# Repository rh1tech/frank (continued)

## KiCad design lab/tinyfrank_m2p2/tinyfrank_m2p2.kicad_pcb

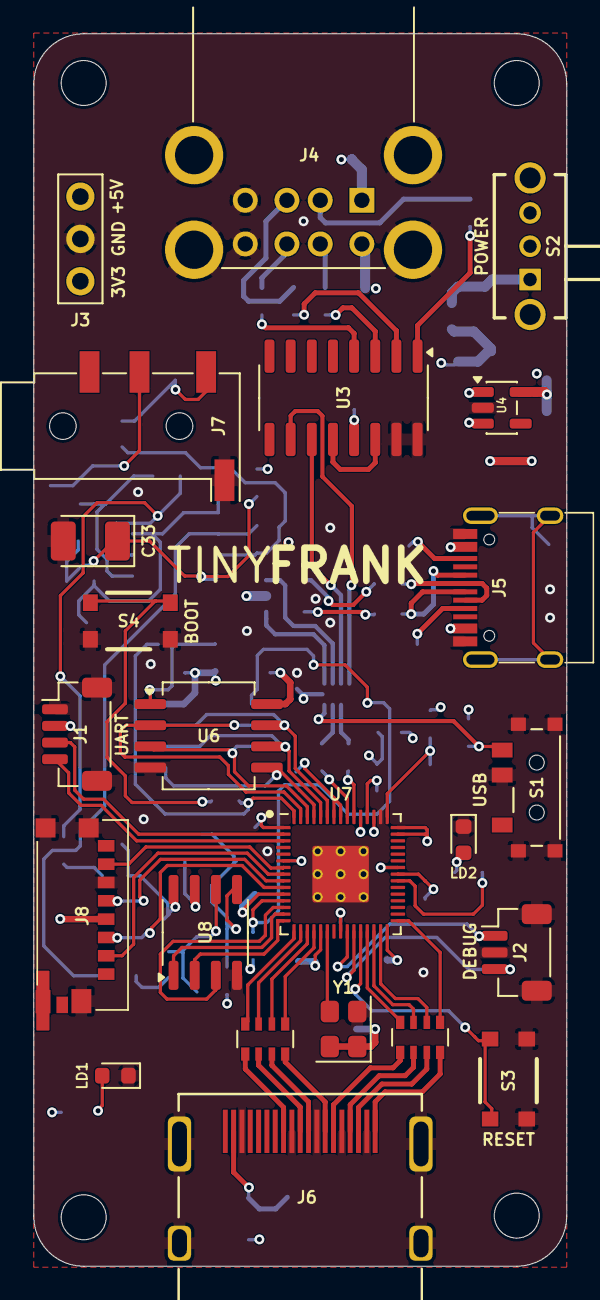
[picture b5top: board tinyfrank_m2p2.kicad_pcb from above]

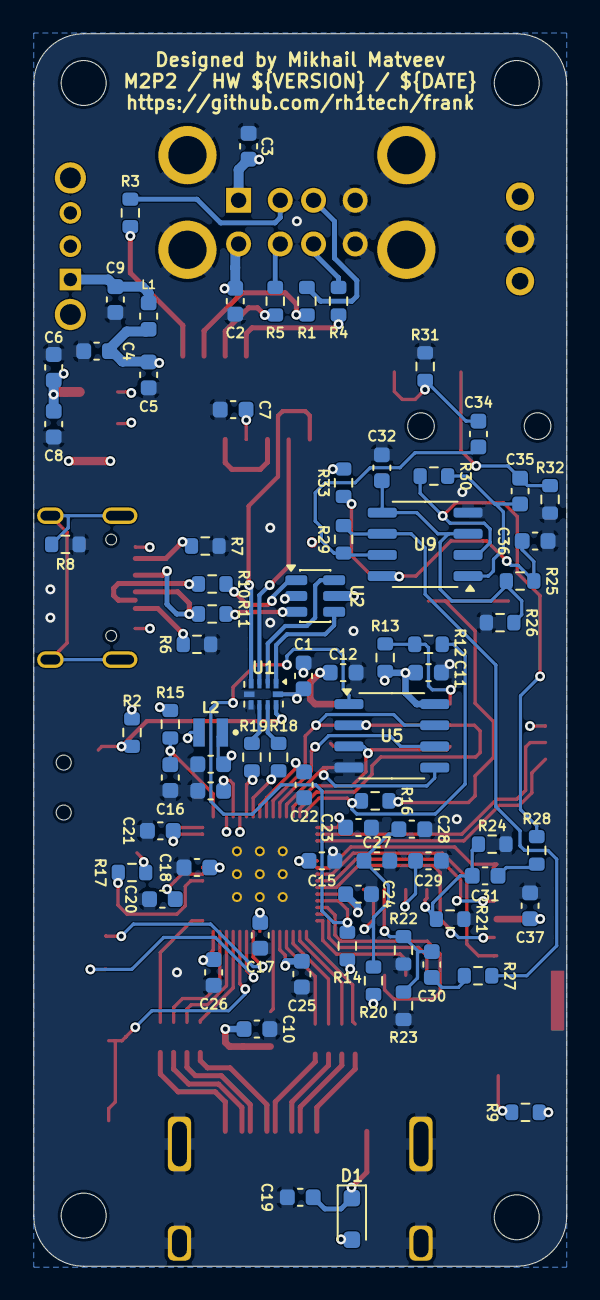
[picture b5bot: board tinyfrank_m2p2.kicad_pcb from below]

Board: 4 copper layers, 32.0 x 74.0 mm, 103 parts (76 on the bottom side), 89 nets.

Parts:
C1, C5, C6, C9, C10, C11, C12, C15, C18, C19, C20, C21, C22, C23, C24, C25, C26, C28, C36, C37: 100n; C_0603_1608Metric
C2, C3, C4, C8, C27, C29, C30, C31, C32, C34, C35: 10u; C_0603_1608Metric
C7, C13, C14, C16, C17: 4.7u; C_0603_1608Metric
C33: 10u; C_3528_Tantalum
D1: 1N5819WS; D_SOD-323
H1, H2, H3, H4: Hole 2.7mm; MountingHole_2.7mm
J1: UART; JST_SH_1x04_P1.00mm_Vertical
J2: DEBUG; JST_SH_1x03_P1.00mm_Vertical
J3: PWR; PinHeader_1x03_P2.54mm
J4: SS-52100-004; USB_A_Stacked
J5: USB4215-03-A; USB_C_Receptacle
J6: DC3RX19JA2; HDMI_Female
J7: PJ-320D; AudioJack_3.5mm_PJ320D
J8: 0475710001; MicroSD_SMD_Short
L1: 330R; L_0603_1608Metric
L2: 3.3u; L_2016_Polarized
LD1: Green; LED_0603_1608Metric
LD2: Blue; LED_0603_1608Metric
R1, R3, R4, R5, R10, R11: 22R; R_0603_1608Metric
R2, R13, R14, R23, R24, R25, R26, R27, R28: 10K; R_0603_1608Metric
R6, R7: 5.1K; R_0603_1608Metric
R8: 1M; R_0603_1608Metric
R9, R16, R17: 1K; R_0603_1608Metric
R12: 0R; R_0603_1608Metric
R15: 33R; R_0603_1608Metric
R18, R19: 27R; R_0603_1608Metric
R20, R33: 100R; R_0603_1608Metric
R21, R22: 470R; R_0603_1608Metric
R29, R30: 47K; R_0603_1608Metric
R31, R32: 20K; R_0603_1608Metric
RN1, RN2: 270R; R_Array_4x0603
S1: MSK12C02; Switch_Slide_MSK12C02
S2: SK12D07VG3NS; Switch_Slide_SK12D07VG3NS
S3, S4: Button; Button_SMD_3x4x2mm
U1: TS3USB221RSER; UQFN-10
U2: USBLC6-2SC6; SOT-23-6
U3: MW7211A; SOP-16_P1.27mm
U4: ME6211C33M5; SOT-23-5
U5: ESP-PSRAM32; SO-8
U6: W25Q128JVS; SOIC-8
U7: RP2350; QFN-60_RP2350A
U8: TDA1387T; SO-8
U9: LM358; SO-8
Y1: ASE-12MHz; Oscillator_SMD_Abracon_ASE-4Pin_3.2x2.5mm

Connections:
+1V1: C14.1, C15.1, C17.1, C18.1, L2.1, U7.6 (DVDD), U7.23 (DVDD), U7.39 (DVDD), U7.50 (VREG_FB)
+3V3: C1.2, C6.1, C8.1, C10.1, C11.1, C12.1, C13.1, C20.1, C21.1, C22.1, C23.1, C24.1, C25.1, C26.1, C37.2, J1.2, J3.1, J8.P4 (VDD), R2.1, R9.2, R13.1, R14.2, R15.1, U1.10 (VCC), U4.5 (V_{OUT}), U5.8 (VCC), U6.8 (VCC), U7.1 (IOVDD), U7.11 (IOVDD), U7.20 (IOVDD), U7.30 (IOVDD), U7.38 (IOVDD), U7.44 (ADC_AVDD), U7.45 (IOVDD), U7.49 (VREG_VIN), U7.53 (USB_OTP_VDD), U7.54 (QSPI_IOVDD), Y1.1 (EN), Y1.4 (Vdd)
/Audio/AMP_OUTL: C34.2, J7.T, R31.2
/Audio/AMP_OUTR: C35.2, J7.R, R32.2
/Audio/TDA_DATA: U7.13 (GPIO9), U8.3 (DATA)
/Audio/TDA_L: C30.1, R22.2, R23.1, U8.6 (A_LEFT)
/Audio/TDA_LRCK: U7.15 (GPIO11), U8.2 (LRCK)
/Audio/TDA_R: C31.1, R21.1, R24.1, U8.8 (A_RIGHT)
/Audio/TDA_SCLK: U7.14 (GPIO10), U8.1 (SCLK)
/HDMI/CLKN: RN1.4 (R4.1), U7.16 (GPIO12)
/HDMI/CLKP: RN1.3 (R3.1), U7.17 (GPIO13)
/HDMI/D0N: RN1.2 (R2.1), U7.18 (GPIO14)
/HDMI/D0P: RN1.1 (R1.1), U7.19 (GPIO15)
/HDMI/D1N: RN2.4 (R4.1), U7.27 (GPIO16)
/HDMI/D1P: RN2.3 (R3.1), U7.28 (GPIO17)
/HDMI/D2N: RN2.2 (R2.1), U7.29 (GPIO18)
/HDMI/D2P: RN2.1 (R1.1), U7.31 (GPIO19)
/Micro SD/CDDAT3: J8.P2 (CD/DAT3), U7.8 (GPIO5)
/Micro SD/CLK: J8.P5 (CLK), U7.9 (GPIO6)
/Micro SD/CMD: J8.P3 (CMD), U7.10 (GPIO7)
/Micro SD/DAT0: J8.P7 (DAT0), U7.7 (GPIO4)
/Power/D1+: U1.1 (1D+), U2.4 (I/O2)
/Power/D1-: U1.2 (1D-), U2.6 (I/O1)
/Power/D2+: U1.3 (2D+), U3.11 (DPU)
/Power/D2-: U1.4 (2D-), U3.10 (DMU)
/Power/D+: R18.1, U1.8 (D+)
/Power/D-: R19.1, U1.7 (D-)
/Power/DS1+: R1.1, U3.2 (DP0)
/Power/DS1-: R3.1, U3.1 (DM0)
/Power/DS2+: R4.1, U3.4 (DP1)
/Power/DS2-: R5.1, U3.3 (DM1)
/Power/S: R2.2, S1.3, U1.9 (S)
/Power/VBUS_IN: J5.2 (VBUS), J5.11 (VBUS), S2.2
/RP2350A/FLASH_SS: R12.2, R13.2, U6.1 (~CS)
/RP2350A/GPIO0: J1.3, U7.2 (GPIO0)
/RP2350A/GPIO1: J1.4, U7.3 (GPIO1)
/RP2350A/GPIO8: R14.1, U5.1 (~CE), U7.12 (GPIO8)
/RP2350A/QSPI_SCLK: U5.6 (SCLK), U6.6 (CLK), U7.56 (QSPI_SCLK)
/RP2350A/QSPI_SD0: U5.5 (SI/SIO), U6.5 (DI(IO0)), U7.57 (QSPI_SD0)
/RP2350A/QSPI_SD1: U5.2 (SO/SIO), U6.2 (DO(IO1)), U7.59 (QSPI_SD1)
/RP2350A/QSPI_SD2: U5.3 (SIO2), U6.3 (IO2), U7.58 (QSPI_SD2)
/RP2350A/QSPI_SD3: U5.7 (SIO3), U6.7 (IO3), U7.55 (QSPI_SD3)
/RP2350A/QSPI_SS: R12.1, R16.1, U7.60 (QSPI_SS)
/RP2350A/SWCLK: J2.1, U7.24 (SWCLK)
/RP2350A/SWD: J2.3, U7.25 (SWD)
/RP2350A/VREG_AVDD: C16.1, R15.2, U7.46 (VREG_AVDD)
/RP2350A/VREG_LX: L2.2, U7.48 (VREG_LX)
/RP2350A/XIN: U7.21 (XIN), Y1.3 (OUT)
/RP2350A/~USB_BOOT: R16.2, S4.2, S4.4
/RP Reset/C1: S3.2, S3.4, U7.26 (RUN)
GND: C1.1, C2.2, C3.2, C4.1, C5.1, C6.2, C7.2, C8.2, C9.2, C10.2, C11.2, C12.2, C13.2, C14.2, C15.2, C16.2, C17.2, C18.2, C19.2, C20.2, C21.2, C22.2, C23.2, C24.2, C25.2, C26.2, C27.2, C28.2, C29.2, C32.1, C33.2, C36.1, C37.1, J1.1, J1.MP (Shield), J2.2, J2.MP (Shield), J3.2, J4.4 (GND1), J4.8 (GND2), J4.SH (Shield), J5.1 (GND), J5.12 (GND), J6.2 (G_D2), J6.5 (G_D1), J6.8 (G_D0), J6.11 (G_CLK), J6.17 (G_DDC/CEC), J6.20 (SHIELD1), J6.21 (SHIELD2), J6.22 (SHIELD3), J6.23 (SHIELD4), J7.S, J8.P6 (VSS), J8.SH (GND_3), LD1.1 (K), LD2.1 (K), R6.1, R7.1, R8.2, R21.2, R22.1, R23.2, R24.2, R26.1, R31.1, R32.1, S1.2, S1.4 (GND_4), S3.1, S3.3, S4.1, S4.3, U1.5 (GND), U1.6 (~OE), U2.2 (GND), U3.15 (GND), U3.16 (GND), U4.2 (V_{SS}), U5.4 (VSS), U6.4 (GND), U7.47 (VREG_PGND), U7.61 (GND), U8.4 (AGND), U9.4 (V-), Y1.2 (GND)
GPIO25: R17.2, U7.37 (GPIO25)
unnamed: C9.1, L1.2, S2.1
unnamed: C30.2, R27.2
unnamed: C31.2, R28.2
unnamed: C34.1, R29.1, U9.7
unnamed: C35.1, R30.1, U9.1
unnamed: C19.1, D1.1 (K), J6.18 (+5V)
unnamed: J4.3 (D1+), R1.2
unnamed: J4.2 (D1-), R3.2
unnamed: J4.7 (D2+), R4.2
unnamed: J4.6 (D2-), R5.2
unnamed: J5.4 (CC1), R6.2
unnamed: J5.10 (CC2), R7.2
unnamed: J5.5 (DN2), J5.7 (DN1), R10.2
unnamed: J5.6 (DP1), J5.8 (DP2), R11.2
unnamed: J5.13 (SHIELD), R8.1
unnamed: J6.12 (CLKN), RN1.5 (R4.2)
unnamed: J6.10 (CLKP), RN1.6 (R3.2)
unnamed: J6.9 (D0N), RN1.7 (R2.2)
unnamed: J6.7 (D0P), RN1.8 (R1.2)
unnamed: J6.6 (D1N), RN2.5 (R4.2)
unnamed: J6.4 (D1P), RN2.6 (R3.2)
unnamed: J6.3 (D2N), RN2.7 (R2.2)
unnamed: J6.1 (D2P), RN2.8 (R1.2)
unnamed: LD1.2 (A), R9.1
unnamed: LD2.2 (A), R17.1
unnamed: R10.1, U2.1 (I/O1)
unnamed: R11.1, U2.3 (I/O2)
unnamed: U3.12 (VD33), U3.14 (VD3)
unnamed: R19.2, U7.51 (USB_DM)
unnamed: R18.2, U7.52 (USB_DP)
unnamed: C29.1, U8.7 (FLT)
unnamed: C27.1, C28.1, R20.1, U8.5 (VA)
unnamed: C32.2, R25.1, R26.2, U9.3 (+), U9.5 (+)
unnamed: R28.1, R30.2, U9.2 (-)
unnamed: R27.1, R29.2, U9.6 (-)
unnamed: C33.1, C36.2, R25.2, R33.2, U9.8 (V+)
VBUS: C2.1, C3.1, C4.2, C5.2, C7.1, D1.2 (A), J3.3, J4.1 (VBUS1), J4.5 (VBUS2), L1.1, R20.2, R33.1, U2.5 (VBUS), U3.13 (VDD5), U4.1 (V_{IN}), U4.3 (CE)

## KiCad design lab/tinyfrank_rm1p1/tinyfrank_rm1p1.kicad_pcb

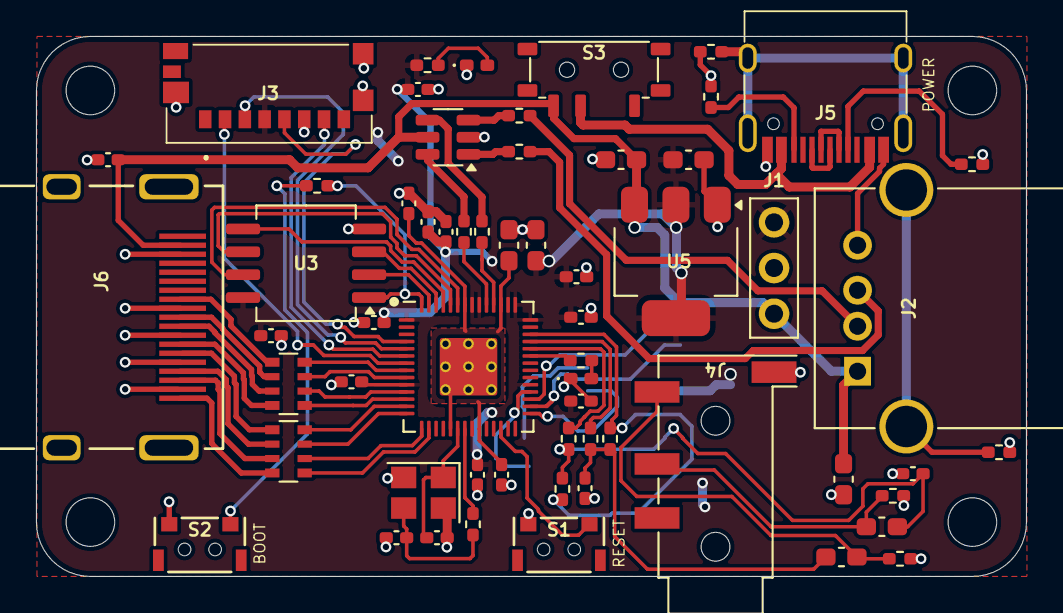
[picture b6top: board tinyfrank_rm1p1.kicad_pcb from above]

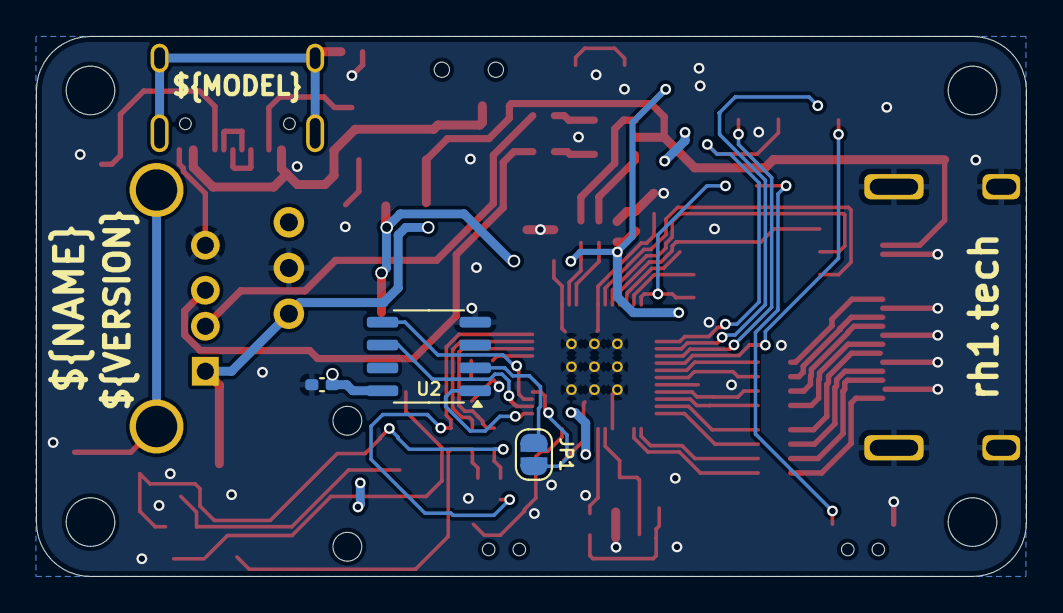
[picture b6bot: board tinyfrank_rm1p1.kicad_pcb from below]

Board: 2 copper layers, 55.0 x 30.0 mm, 67 parts (3 on the bottom side), 65 nets.

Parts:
C1, C3, C5, C23, C24: 10u; Capacitor (0603)
C2, C7, C8, C9, C10, C11, C12, C13, C14, C15, C16, C17, C20, C25: 100n; Capacitor (0402)
C4, C6: 10n; Capacitor (0402)
C18, C19: 1u; Capacitor (0603)
C21, C22: 15p; Capacitor (0402)
H1, H2, H3, H4: MountingHole; Mounting Hole (2.7mm)
J1: PWR; Pin Header (1x03)
J2: 676430910; USB Type A (single)
J3: 0475710001; MicroSD (SMD, short)
J4: PJ-320D; Jack (3.5mm, PJ-320D)
J5: USB4215-03-A; USB Type C
J6: DC3RX19JA2; HDMI (female)
JP1: Jumper (Solder); Jumper (solder)
LD1: Blue; LED (0402)
LD2: Power; LED (0402)
R1, R2: 22R; Resistor (0402)
R3, R17: 1M; Resistor (0402)
R4, R8, R11, R13, R14, R18: 1K; Resistor (0402)
R5, R9: 330R; Resistor (0402)
R6, R7: 2K; Resistor (0402)
R10, R12: 27R; Resistor (0402)
R15, R16: 5.1K; Resistor (0402)
RN1, RN2: 270R; Resistor Array (4x0603)
S1: Reset; TACT-SIDE-4623
S2: Boot; TACT-SIDE-4623
S3: MSK12C02; Switch (MSK12C02)
U1: USBLC6-2SC6; SOT-23-6
U2: ESP-PSRAM32; SO-8
U3: W25Q128JVSIQ; SOIC-8
U4: RP2040; QFN 56
U5: NCP1117 3.3; SOT-223
Y1: 12 MHz; Crystal (3225)

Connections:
+3V3: C2.2, C7.1, C10.1, C11.1, C12.1, C13.1, C14.1, C15.1, C16.1, C17.1, C19.1, C20.1, C23.1, J1.1, J3.P4 (VDD), R18.2, U2.8 (VCC), U3.8 (VCC), U4.1 (IOVDD), U4.10 (IOVDD), U4.22 (IOVDD), U4.33 (IOVDD), U4.42 (IOVDD), U4.43 (ADC_AVDD), U4.44 (VREG_IN), U4.48 (USB_VDD), U4.49 (IOVDD), U5.2 (VO)
/Audio Out/L: C3.1, J4.T, R5.1
/Audio Out/R: C5.1, J4.R, R9.1
/GPIO2: J3.P5 (CLK), U4.4 (GPIO2)
/GPIO3: J3.P3 (CMD), U4.5 (GPIO3)
/GPIO4: J3.P7 (DAT0), U4.6 (GPIO4)
/GPIO5: J3.P2 (CD/DAT3), U4.7 (GPIO5)
/GPIO6: RN1.4 (R4.1), U4.8 (GPIO6)
/GPIO7: RN1.3 (R3.1), U4.9 (GPIO7)
/GPIO8: RN1.2 (R2.1), U4.11 (GPIO8)
/GPIO9: RN1.1 (R1.1), U4.12 (GPIO9)
/GPIO10: RN2.4 (R4.1), U4.13 (GPIO10)
/GPIO11: RN2.3 (R3.1), U4.14 (GPIO11)
/GPIO12: RN2.2 (R2.1), U4.15 (GPIO12)
/GPIO13: RN2.1 (R1.1), U4.16 (GPIO13)
/GPIO18: U2.1 (~CE), U4.29 (GPIO18)
/GPIO19: U2.6 (SCLK), U4.30 (GPIO19)
/GPIO20: U2.5 (SI/SIO), U4.31 (GPIO20)
/GPIO21: JP1.2 (B), U4.32 (GPIO21)
/GPIO25: R14.2, U4.37 (GPIO25)
/GPIO26: R8.2, U4.38 (GPIO26_ADC0)
/GPIO27: R4.2, U4.39 (GPIO27_ADC1)
/GPIO28: R6.2, R7.2, U4.40 (GPIO28_ADC2)
/PW_D+: R10.1, U1.6 (I/O1)
/PW_D-: R12.1, U1.4 (I/O2)
/RP2040/QSPI_SCLK: U3.6 (CLK), U4.52 (QSPI_SCLK)
/RP2040/QSPI_SD0: U3.5 (DI(IO0)), U4.53 (QSPI_SD0)
/RP2040/QSPI_SD1: U3.2 (DO(IO1)), U4.55 (QSPI_SD1)
/RP2040/QSPI_SD2: U3.3 (IO2), U4.54 (QSPI_SD2)
/RP2040/QSPI_SD3: U3.7 (IO3), U4.51 (QSPI_SD3)
/RP2040/QSPI_SS: R11.1, U3.1 (~CS), U4.56 (QSPI_SS)
/RP2040/XIN: C22.1, U4.20 (XIN), Y1.1
/RP2040/XOUT: R13.1, U4.21 (XOUT)
/RUN: S1.1, U4.26 (RUN)
GND: C1.2, C2.1, C4.2, C6.2, C7.2, C8.2, C9.2, C10.2, C11.2, C12.2, C13.2, C14.2, C15.2, C16.2, C17.2, C18.2, C19.2, C20.2, C21.2, C22.2, C23.2, C24.2, C25.2, J1.2, J2.4 (GND), J3.G1 (GND_1), J3.G2 (GND_2), J3.G3 (GND_3), J3.P6 (VSS), J4.S, J5.1 (GND), J5.12 (GND), J6.2 (G_D2), J6.5 (G_D1), J6.8 (G_D0), J6.11 (G_CLK), J6.17 (G_DDC/CEC), J6.20 (SHIELD1), J6.21 (SHIELD2), J6.22 (SHIELD3), J6.23 (SHIELD4), LD1.1 (K), LD2.1 (K), R3.2, R5.2, R9.2, R15.1, R16.1, R17.2, S1.2, S2.2, U1.2 (GND), U2.4 (VSS), U3.4 (GND), U4.19 (TESTEN), U4.57 (GND), U5.1 (GND), Y1.2, Y1.4
unnamed: C3.2, C4.1, R4.1, R6.1
unnamed: C5.2, C6.1, R7.1, R8.1
unnamed: C21.1, R13.2, Y1.3
unnamed: J2.3 (D+), R1.2
unnamed: J2.2 (D-), R2.2
unnamed: J2.5 (Shield), R3.1
unnamed: J5.4 (CC1), R15.2
unnamed: J5.10 (CC2), R16.2
unnamed: J5.5 (DN2), J5.7 (DN1)
unnamed: J5.6 (DP1), J5.8 (DP2)
unnamed: J5.13 (SHIELD), R17.1
unnamed: J6.12 (CLKN), RN1.5 (R4.2)
unnamed: J6.10 (CLKP), RN1.6 (R3.2)
unnamed: J6.9 (D0N), RN1.7 (R2.2)
unnamed: J6.7 (D0P), RN1.8 (R1.2)
unnamed: J6.6 (D1N), RN2.5 (R4.2)
unnamed: J6.4 (D1P), RN2.6 (R3.2)
unnamed: J6.3 (D2N), RN2.7 (R2.2)
unnamed: J6.1 (D2P), RN2.8 (R1.2)
unnamed: JP1.1 (A), U2.2 (SO/SIO)
unnamed: LD1.2 (A), R14.1
unnamed: LD2.2 (A), R18.1
unnamed: R1.1, U1.1 (I/O1)
unnamed: R2.1, U1.3 (I/O2)
unnamed: R11.2, S2.1
unnamed: J5.2 (VBUS), J5.11 (VBUS), S3.2 (B)
unnamed: R12.2, U4.46 (USB_DM)
unnamed: R10.2, U4.47 (USB_DP)
unnamed: C8.1, C9.1, C18.1, U4.23 (DVDD), U4.45 (VREG_VOUT), U4.50 (DVDD)
VBUS: C1.1, C24.1, C25.1, J1.3, J2.1 (VBUS), J6.18 (+5V), S3.3 (A), U1.5 (VBUS), U5.3 (VI)

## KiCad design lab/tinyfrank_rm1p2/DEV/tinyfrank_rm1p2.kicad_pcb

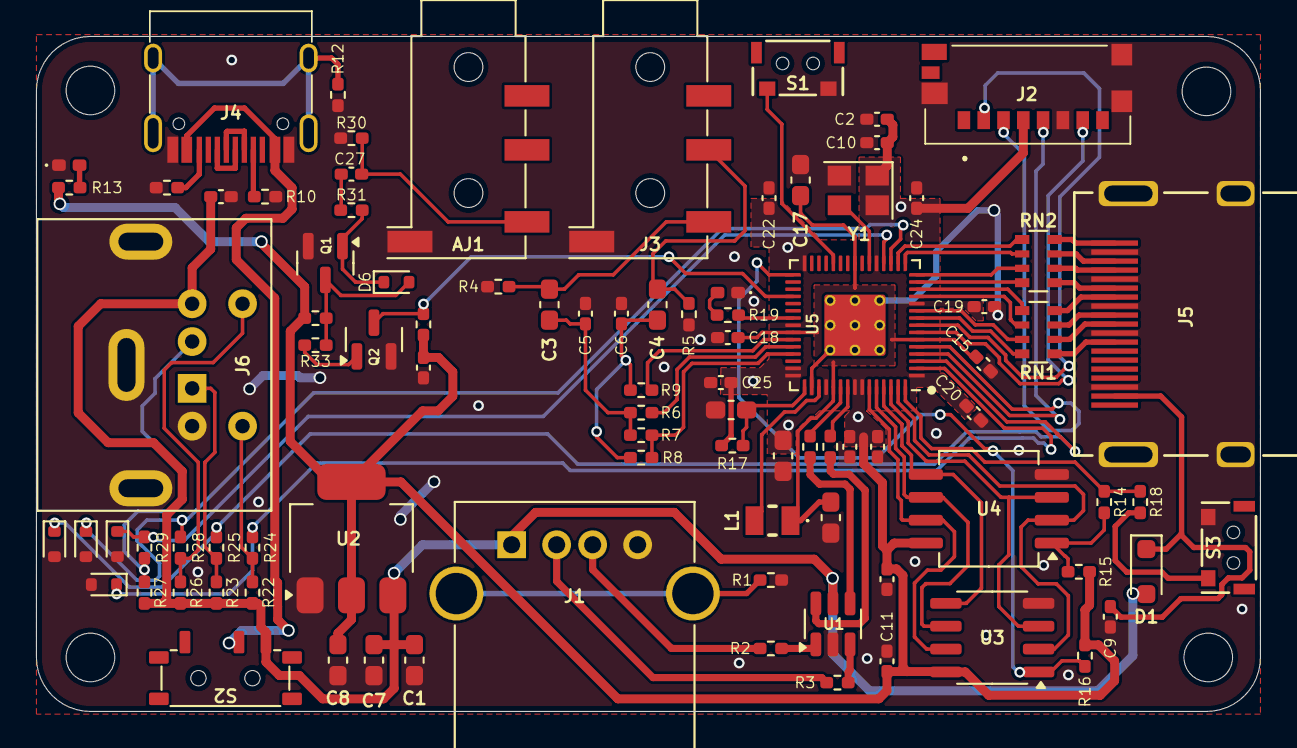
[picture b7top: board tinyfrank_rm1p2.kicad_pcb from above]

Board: 2 copper layers, 68.0 x 37.5 mm, 95 parts (0 on the bottom side), 77 nets.

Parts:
AJ1: PJ-320D; Jack (3.5mm, PJ-320D)
C1, C3, C4, C7, C8: 10u; Capacitor (0603)
C2, C9, C10, C11, C12, C15, C18, C19, C20, C21, C22, C23, C24, C25, C26, C27, C28: 100n; Capacitor (0402)
C5, C6: 10n; Capacitor (0402)
C13, C14, C16, C17: 4.7u; Capacitor (0603)
D1: 1N5819WS; Diode (SOD-323)
D2, D3, D4, D5: 3V3; Diode (SOD-523)
D6: 1N4148; Diode (SOD-523)
H1, H2, H3, H4: MountingHole; Mounting Hole (2.7mm)
J1: 676430910; USB Type A (single)
J2: 0475710001; MicroSD (SMD, short)
J3: PJ-320D; Jack (3.5mm, PJ-320D)
J4: USB4215-03-A; USB Type C
J5: DC3RX19JA2; HDMI (female)
J6: MDC-036; MiniDIN (6 Pin, female)
L1: 3.3u; Inductor (0806)
LD1: Power; LED (0402)
LD2: Blue; LED (0402)
Q1, Q2: BC850; SOT-23
R1, R12: 1M; Resistor (0402)
R2, R3: 22R; Resistor (0402)
R4, R5: 330R; Resistor (0402)
R6, R9, R13, R18, R19, R22, R23, R26, R27, R34: 1K; Resistor (0402)
R7, R8: 2K; Resistor (0402)
R10, R11: 5.1K; Resistor (0402)
R14: 0R; Resistor (0402)
R15, R16, R31, R32, R33: 10K; Resistor (0402)
R17: 33R; Resistor (0402)
R20, R21: 27R; Resistor (0402)
R24, R25, R28, R29, R30: 100R; Resistor (0402)
RN1, RN2: 270R; Resistor Array (4x0603)
S1: Reset; TACT-SIDE-4623
S2: MSK12C02; Switch (MSK12C02)
S3: Boot 2350; TACT-SIDE-4623
U1: USBLC6-2SC6; SOT-23-6
U2: NCP1117 3.3; SOT-223
U3: ESP-PSRAM32; SO-8
U4: W25Q128JVS; SOIC-8
U5: RP2350; QFN 60 (RP2350A)
Y1: ASE-12MHz; Crystal (3225, active)

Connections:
+1V1: C14.1, C15.1, C17.1, C18.1, L1.1, U5.6 (DVDD), U5.23 (DVDD), U5.39 (DVDD), U5.50 (VREG_FB)
+3V3: C2.2, C8.1, C10.1, C11.1, C12.1, C13.1, C19.1, C20.1, C21.1, C22.1, C23.1, C24.1, C25.1, C28.1, J2.P4 (VDD), R13.2, R15.1, R16.2, R17.1, R32.1, R34.1, U2.2 (VO), U3.8 (VCC), U4.8 (VCC), U5.1 (IOVDD), U5.11 (IOVDD), U5.20 (IOVDD), U5.30 (IOVDD), U5.38 (IOVDD), U5.44 (ADC_AVDD), U5.45 (IOVDD), U5.49 (VREG_VIN), U5.53 (USB_OTP_VDD), U5.54 (QSPI_IOVDD), Y1.1 (EN), Y1.4 (Vdd)
/Audio Out/L: C3.1, J3.T, R4.1
/Audio Out/R: C4.1, J3.R, R5.1
/D+: R20.1, U1.6 (I/O1)
/D-: R21.1, U1.4 (I/O2)
/GPIO0: D2.1 (K), R24.2, U5.2 (GPIO0)
/GPIO1: D3.1 (K), R25.2, U5.3 (GPIO1)
/GPIO2: J2.P5 (CLK), U5.4 (GPIO2)
/GPIO3: J2.P3 (CMD), U5.5 (GPIO3)
/GPIO4: J2.P7 (DAT0), U5.7 (GPIO4)
/GPIO5: J2.P2 (CD/DAT3), U5.8 (GPIO5)
/GPIO6: RN1.4 (R4.1), U5.9 (GPIO6)
/GPIO7: RN1.3 (R3.1), U5.10 (GPIO7)
/GPIO8: RN1.2 (R2.1), U5.12 (GPIO8)
/GPIO9: RN1.1 (R1.1), U5.13 (GPIO9)
/GPIO10: RN2.4 (R4.1), U5.14 (GPIO10)
/GPIO11: RN2.3 (R3.1), U5.15 (GPIO11)
/GPIO12: RN2.2 (R2.1), U5.16 (GPIO12)
/GPIO13: RN2.1 (R1.1), U5.17 (GPIO13)
/GPIO14: D4.1 (K), R28.2, U5.18 (GPIO14)
/GPIO15: D5.1 (K), R29.2, U5.19 (GPIO15)
/GPIO19: R16.1, U3.1 (~CE), U5.31 (GPIO19)
/GPIO22: Q2.3 (C), R34.2, U5.34 (GPIO22)
/GPIO26: R9.2, U5.40 (GPIO26_ADC0)
/GPIO27: R6.2, U5.41 (GPIO27_ADC1)
/GPIO28: R7.2, R8.2, U5.42 (GPIO28_ADC2)
/PS2/PS2_KB_CLK: J6.5, R22.1, R24.1
/PS2/PS2_KB_DATA: J6.1, R23.1, R25.1
/PS2/PS2_MS_CLK: J6.6, R26.1, R28.1
/PS2/PS2_MS_DATA: J6.2, R27.1, R29.1
/RP2350A/FLASH_SS: R14.2, R15.2, U4.1 (~CS)
/RP2350A/QSPI_SCLK: U3.6 (SCLK), U4.6 (CLK), U5.56 (QSPI_SCLK)
/RP2350A/QSPI_SD0: U3.5 (SI/SIO), U4.5 (DI(IO0)), U5.57 (QSPI_SD0)
/RP2350A/QSPI_SD1: U3.2 (SO/SIO), U4.2 (DO(IO1)), U5.59 (QSPI_SD1)
/RP2350A/QSPI_SD2: U3.3 (SIO2), U4.3 (IO2), U5.58 (QSPI_SD2)
/RP2350A/QSPI_SD3: U3.7 (SIO3), U4.7 (IO3), U5.55 (QSPI_SD3)
/RP2350A/QSPI_SS: R14.1, R18.1, U5.60 (QSPI_SS)
/RP2350A/VREG_AVDD: C16.1, R17.2, U5.46 (VREG_AVDD)
/RP2350A/VREG_LX: L1.2, U5.48 (VREG_LX)
/RP2350A/XIN: U5.21 (XIN), Y1.3 (OUT)
/RP2350A/~USB_BOOT: R18.2, S3.2
/RUN: S1.1, U5.26 (RUN)
GND: AJ1.S, C1.2, C2.1, C5.2, C6.2, C7.2, C8.2, C9.2, C10.2, C11.2, C12.2, C13.2, C14.2, C15.2, C16.2, C17.2, C18.2, C19.2, C20.2, C21.2, C22.2, C23.2, C24.2, C25.2, C26.2, C28.2, D2.2 (A), D3.2 (A), D4.2 (A), D5.2 (A), J1.4 (GND), J2.G1 (GND_1), J2.G2 (GND_2), J2.G3 (GND_3), J2.P6 (VSS), J3.S, J4.1 (GND), J4.12 (GND), J5.2 (G_D2), J5.5 (G_D1), J5.8 (G_D0), J5.11 (G_CLK), J5.17 (G_DDC/CEC), J5.20 (SHIELD1), J5.21 (SHIELD2), J5.22 (SHIELD3), J5.23 (SHIELD4), J6.3, LD1.1 (K), LD2.1 (K), Q1.2 (E), Q2.2 (E), R1.2, R4.2, R5.2, R10.1, R11.1, R12.2, R30.2, S1.2, S3.1, U1.2 (GND), U2.1 (GND), U3.4 (VSS), U4.4 (GND), U5.47 (VREG_PGND), U5.61 (GND), Y1.2 (GND)
GPIO25: R19.2, U5.37 (GPIO25)
unnamed: AJ1.T, C27.1, R30.1
unnamed: C3.2, C5.1, R6.1, R7.1
unnamed: C4.2, C6.1, R8.1, R9.1
unnamed: C27.2, R31.1
unnamed: C9.1, D1.1 (K), J5.18 (+5V)
unnamed: D6.2 (A), Q1.3 (C), R32.2, R33.1
unnamed: D6.1 (K), Q1.1 (B), R31.2
unnamed: J1.3 (D+), R2.2
unnamed: J1.2 (D-), R3.2
unnamed: J1.5 (Shield), R1.1
unnamed: J4.4 (CC1), R10.2
unnamed: J4.10 (CC2), R11.2
unnamed: J4.5 (DN2), J4.7 (DN1)
unnamed: J4.6 (DP1), J4.8 (DP2)
unnamed: J4.13 (SHIELD), R12.1
unnamed: J5.12 (CLKN), RN1.5 (R4.2)
unnamed: J5.10 (CLKP), RN1.6 (R3.2)
unnamed: J5.9 (D0N), RN1.7 (R2.2)
unnamed: J5.7 (D0P), RN1.8 (R1.2)
unnamed: J5.6 (D1N), RN2.5 (R4.2)
unnamed: J5.4 (D1P), RN2.6 (R3.2)
unnamed: J5.3 (D2N), RN2.7 (R2.2)
unnamed: J5.1 (D2P), RN2.8 (R1.2)
unnamed: LD1.2 (A), R13.1
unnamed: LD2.2 (A), R19.1
unnamed: Q2.1 (B), R33.2
unnamed: R2.1, U1.1 (I/O1)
unnamed: R3.1, U1.3 (I/O2)
unnamed: J4.2 (VBUS), J4.11 (VBUS), S2.2 (B)
unnamed: R21.2, U5.51 (USB_DM)
unnamed: R20.2, U5.52 (USB_DP)
VBUS: C1.1, C7.1, C26.1, D1.2 (A), J1.1 (VBUS), J6.4, R22.2, R23.2, R26.2, R27.2, S2.3 (A), U1.5 (VBUS), U2.3 (VI)
